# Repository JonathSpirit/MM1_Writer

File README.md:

# MM1_Writer

Copyright (C) 2021 Guillaume Guillet\
Licensed under CERN-OHL-W v2 or later

<table border="0px">
<tr>
<td>
This source describes Open Hardware and is licensed under the CERN-OHL-W v2 or later.
</td>
</tr>
<tr>
<td>
You may redistribute and modify this documentation and make products
using it under the terms of the CERN-OHL-W v2 (https:/cern.ch/cern-ohl).
This documentation is distributed WITHOUT ANY EXPRESS OR IMPLIED
WARRANTY, INCLUDING OF MERCHANTABILITY, SATISFACTORY QUALITY
AND FITNESS FOR A PARTICULAR PURPOSE. Please see the CERN-OHL-W v2
for applicable conditions.
</td>
</tr>
</table>

Made with [Kicad](https://kicad.org/)

## Description
This is a board helper for programming memory module that follow [MM1 standard](https://github.com/JonathSpirit/GComputer_standard).\
You can find the uc code here : [MM1_Writer_code](https://github.com/JonathSpirit/MM1_Writer_code).

## Stats

\
\
\

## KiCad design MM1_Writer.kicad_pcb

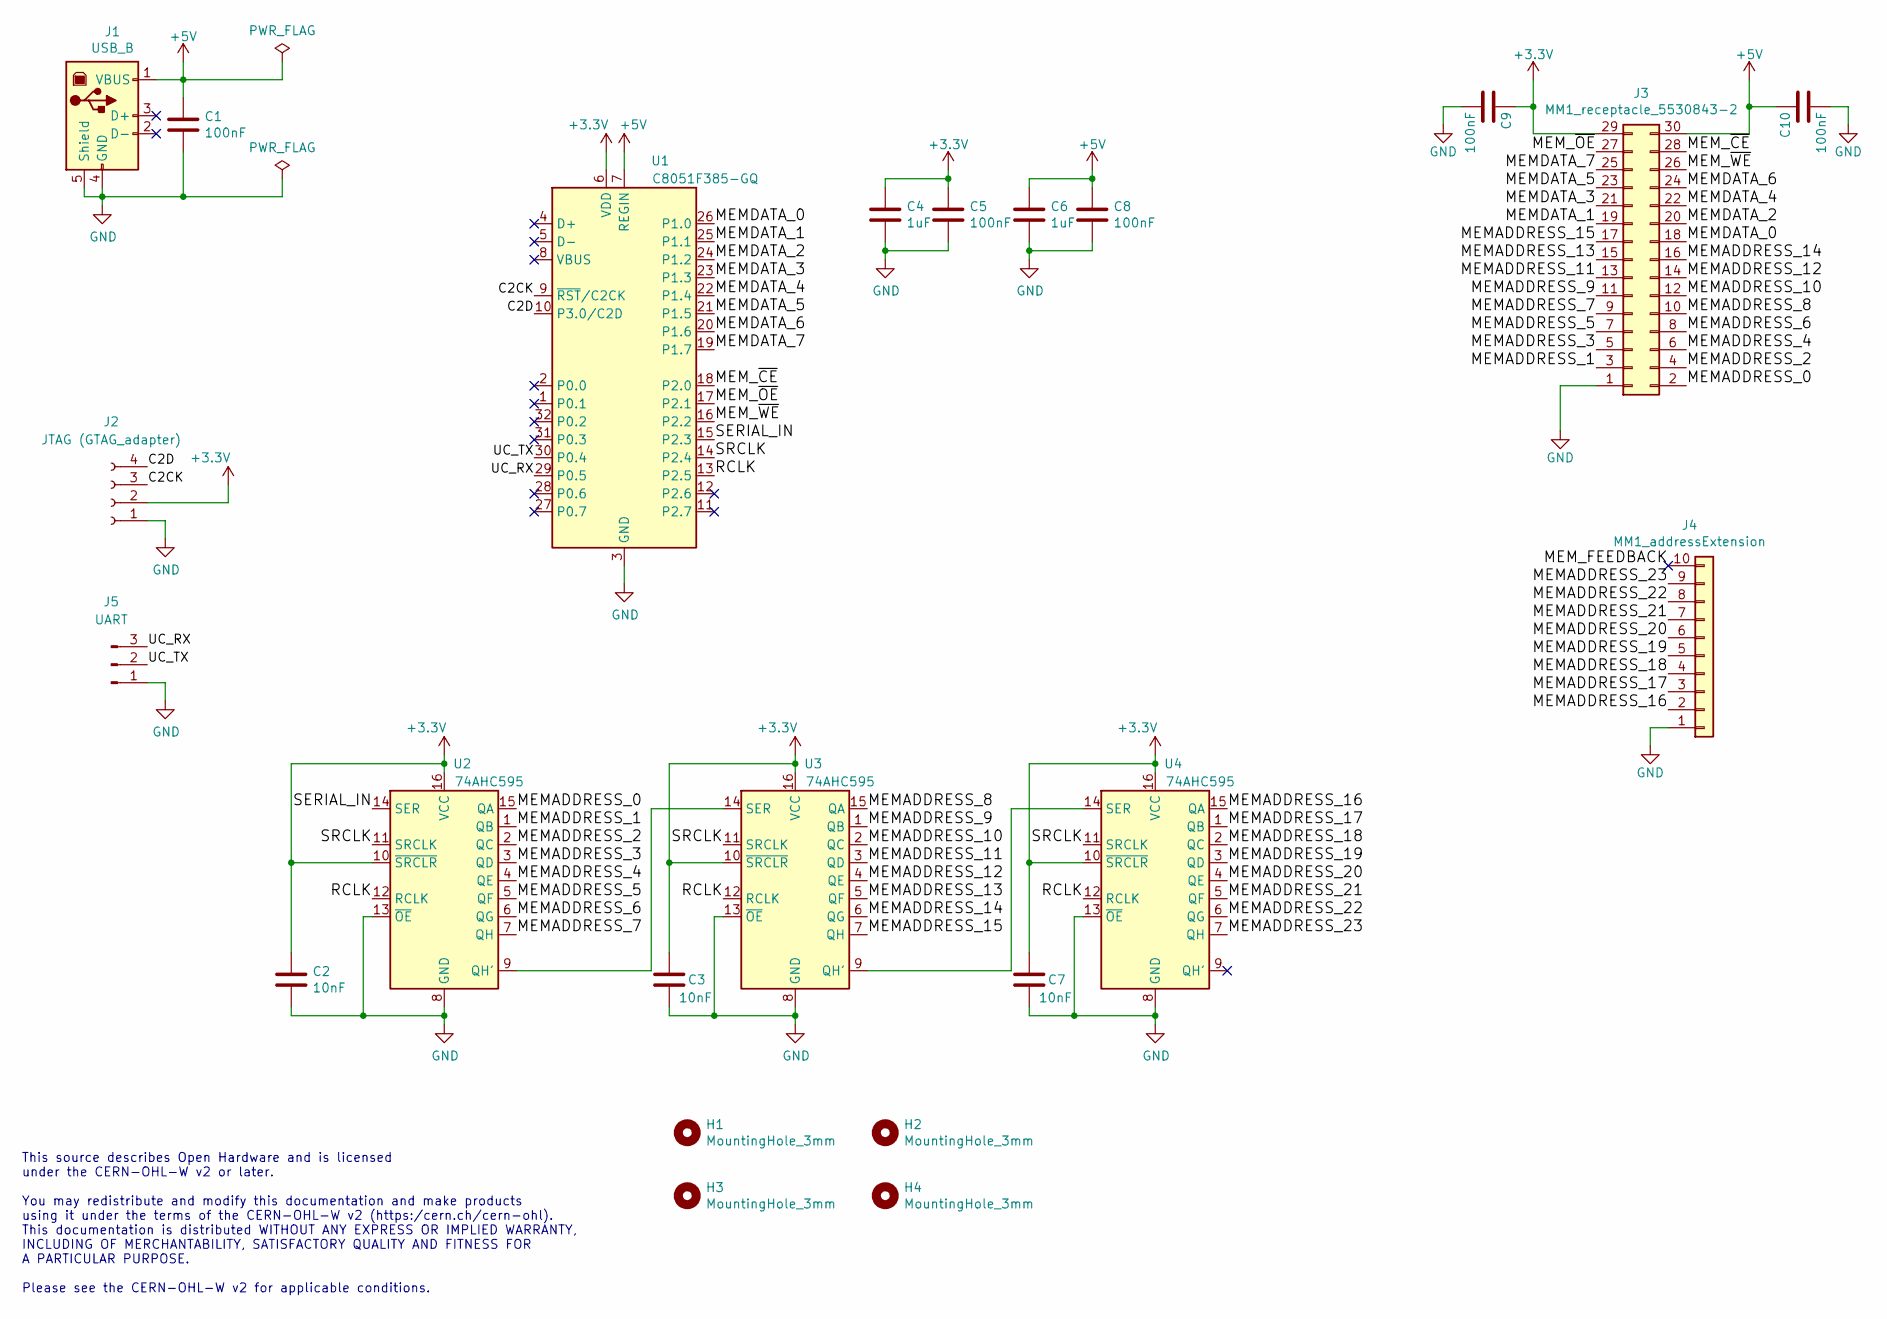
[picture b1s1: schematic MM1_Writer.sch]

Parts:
C1, C5, C8, C9, C10: 100nF; C_0805_2012Metric
C2, C3, C7: 10nF; C_0805_2012Metric
C4, C6: 1uF; C_0805_2012Metric
H1, H2, H3, H4: MountingHole_3mm
J1: USB_B; USB_B_OST_USB-B1HSxx_Horizontal
J2: JTAG (GTAG_adapter); PinSocket_1x04_P2.54mm_Horizontal
J3: MM1_receptacle_5530843-2; TE_5530843-2
J4: MM1_addressExtension; IDC-Header_2x05_P2.54mm_Vertical
J5: UART; PinHeader_1x03_P2.54mm_Horizontal
U1: C8051F385-GQ; LQFP-32_7x7mm_P0.8mm
U2, U3, U4: 74AHC595; SOIC-16_3.9x9.9mm_P1.27mm

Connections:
+3V3: C2.1, C3.1, C4.1, C5.1, C7.1, C9.1, J2.2, J3.29, U1.6 (VDD), U2.10 (~SRCLR), U2.16 (VCC), U3.10 (~SRCLR), U3.16 (VCC), U4.10 (~SRCLR), U4.16 (VCC)
+5V: C1.1, C6.1, C8.1, C10.1, J1.1 (VBUS), J3.30, U1.7 (REGIN)
/C2CK: J2.3, U1.9 (~RST~/C2CK)
/C2D: J2.4, U1.10 (P3.0/C2D)
/MEMADDRESS_0: J3.2, U2.15 (QA)
/MEMADDRESS_1: J3.3, U2.1 (QB)
/MEMADDRESS_2: J3.4, U2.2 (QC)
/MEMADDRESS_3: J3.5, U2.3 (QD)
/MEMADDRESS_4: J3.6, U2.4 (QE)
/MEMADDRESS_5: J3.7, U2.5 (QF)
/MEMADDRESS_6: J3.8, U2.6 (QG)
/MEMADDRESS_7: J3.9, U2.7 (QH)
/MEMADDRESS_8: J3.10, U3.15 (QA)
/MEMADDRESS_9: J3.11, U3.1 (QB)
/MEMADDRESS_10: J3.12, U3.2 (QC)
/MEMADDRESS_11: J3.13, U3.3 (QD)
/MEMADDRESS_12: J3.14, U3.4 (QE)
/MEMADDRESS_13: J3.15, U3.5 (QF)
/MEMADDRESS_14: J3.16, U3.6 (QG)
/MEMADDRESS_15: J3.17, U3.7 (QH)
/MEMADDRESS_16: J4.2, U4.15 (QA)
/MEMADDRESS_17: J4.3, U4.1 (QB)
/MEMADDRESS_18: J4.4, U4.2 (QC)
/MEMADDRESS_19: J4.5, U4.3 (QD)
/MEMADDRESS_20: J4.6, U4.4 (QE)
/MEMADDRESS_21: J4.7, U4.5 (QF)
/MEMADDRESS_22: J4.8, U4.6 (QG)
/MEMADDRESS_23: J4.9, U4.7 (QH)
/MEMDATA_0: J3.18, U1.26 (P1.0)
/MEMDATA_1: J3.19, U1.25 (P1.1)
/MEMDATA_2: J3.20, U1.24 (P1.2)
/MEMDATA_3: J3.21, U1.23 (P1.3)
/MEMDATA_4: J3.22, U1.22 (P1.4)
/MEMDATA_5: J3.23, U1.21 (P1.5)
/MEMDATA_6: J3.24, U1.20 (P1.6)
/MEMDATA_7: J3.25, U1.19 (P1.7)
/MEM_FEEDBACK: J4.10
/MEM_~CE: J3.28, U1.18 (P2.0)
/MEM_~OE: J3.27, U1.17 (P2.1)
/MEM_~WE: J3.26, U1.16 (P2.2)
/RCLK: U1.13 (P2.5), U2.12 (RCLK), U3.12 (RCLK), U4.12 (RCLK)
/SERIAL_IN: U1.15 (P2.3), U2.14 (SER)
/SRCLK: U1.14 (P2.4), U2.11 (SRCLK), U3.11 (SRCLK), U4.11 (SRCLK)
/UC_RX: J5.3, U1.29 (P0.5)
/UC_TX: J5.2, U1.30 (P0.4)
GND: C1.2, C2.2, C3.2, C4.2, C5.2, C6.2, C7.2, C8.2, C9.2, C10.2, J1.4 (GND), J1.5 (Shield), J2.1, J3.1, J4.1, J5.1, U1.3 (GND), U2.8 (GND), U2.13 (~OE), U3.8 (GND), U3.13 (~OE), U4.8 (GND), U4.13 (~OE)
unnamed: U2.9 (QH'), U3.14 (SER)
unnamed: U3.9 (QH'), U4.14 (SER)

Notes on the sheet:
This source describes Open Hardware and is licensed under the CERN-OHL-W v2 or later. You may redistribute and modify this documentation and make products using it under the terms of the CERN-OHL-W v2 (https:/cern.ch/cern-ohl). This documentation is distributed WITHOUT ANY EXPRESS OR IMPLIED WARRAN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

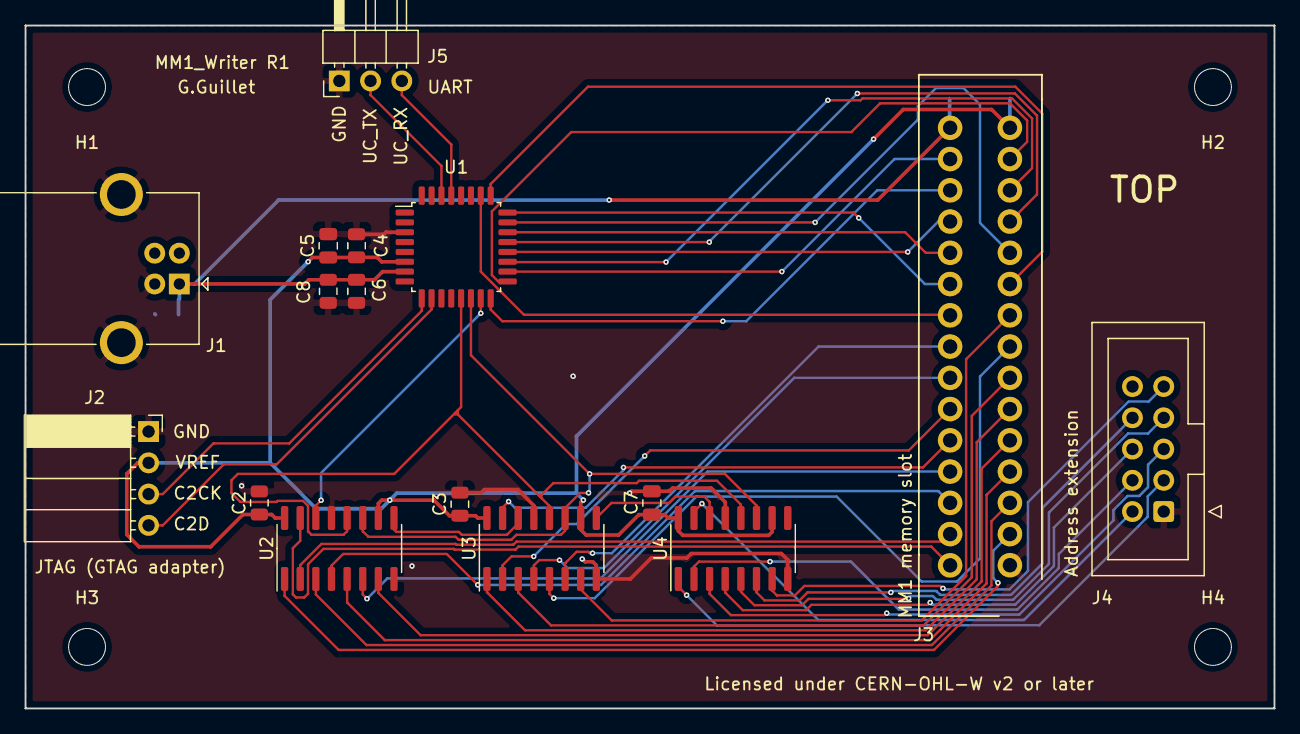
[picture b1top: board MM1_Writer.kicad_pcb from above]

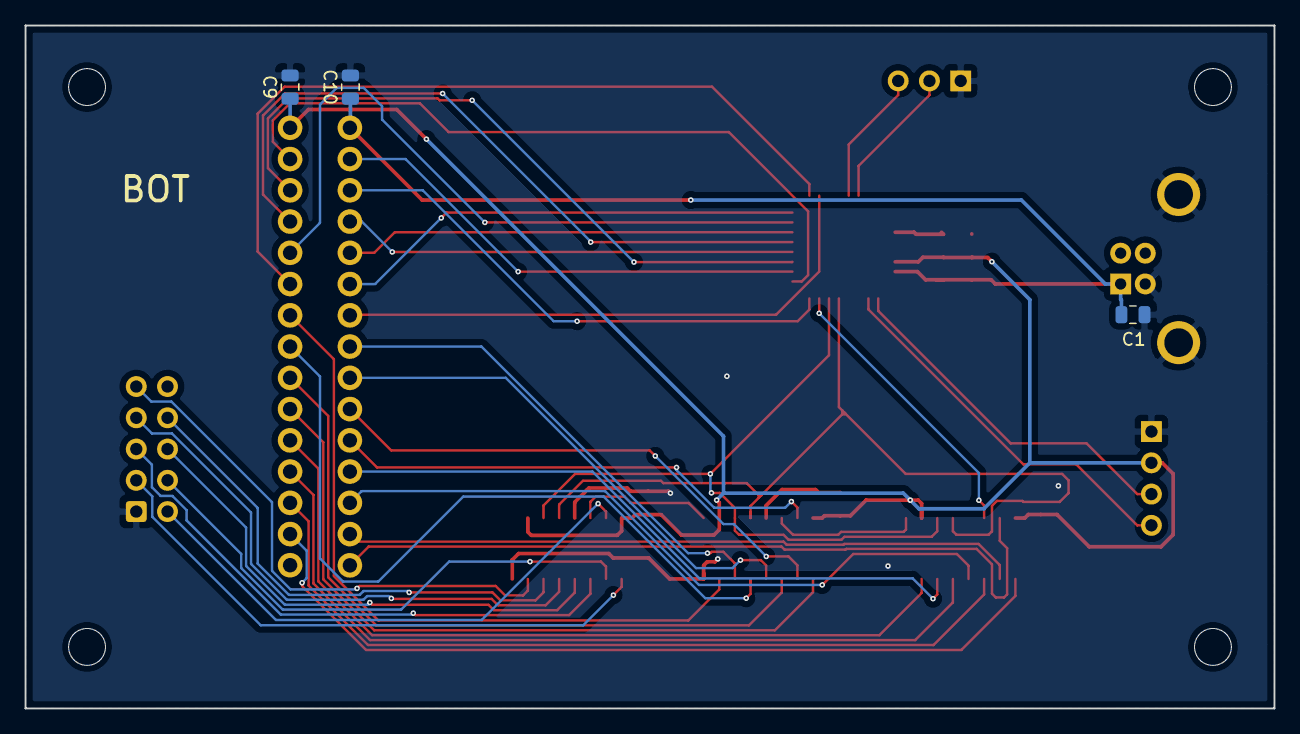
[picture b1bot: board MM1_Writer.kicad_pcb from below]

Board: 2 copper layers, 101.5 x 55.5 mm, 23 parts (3 on the bottom side), 47 nets.

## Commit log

2020-11-26 add .gitignore
2020-11-26 first push

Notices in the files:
MM1_Writer.kicad_pcb:
Copyright Guillaume Guillet 2020
